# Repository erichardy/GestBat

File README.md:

# GestBat
Boîtier d'aide à la mise en charge des batteries de mon Vélo à Assistance Electrique (VAE)

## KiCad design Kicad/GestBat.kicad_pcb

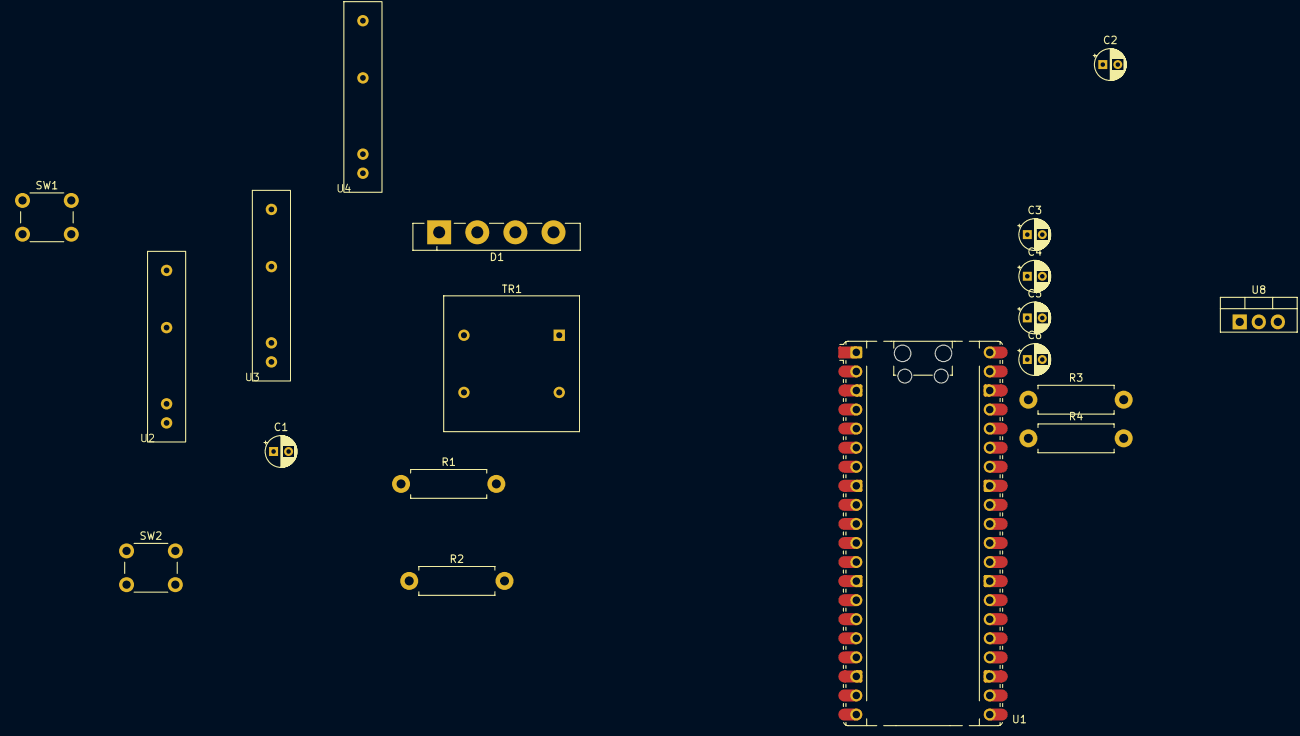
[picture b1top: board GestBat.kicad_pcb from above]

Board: 2 copper layers, 19 parts (0 on the bottom side), 14 nets, no tracks yet.

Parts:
C1, C5, C6: c=10u; CP_Radial_D4.0mm_P2.00mm
C2: c=1u; CP_Radial_D4.0mm_P2.00mm
C3, C4: c=1000u; CP_Radial_D4.0mm_P2.00mm
D1: GBU4M; Diode_Bridge_Vishay_GBU
R1: r=1M; R_Axial_DIN0411_L9.9mm_D3.6mm_P12.70mm_Horizontal
R2: r=6.8k; R_Axial_DIN0411_L9.9mm_D3.6mm_P12.70mm_Horizontal
R3: r=3.3k; R_Axial_DIN0411_L9.9mm_D3.6mm_P12.70mm_Horizontal
R4: r=1k; R_Axial_DIN0411_L9.9mm_D3.6mm_P12.70mm_Horizontal
SW1, SW2: SW_Push; SW_PUSH_6mm_H5mm
TR1: TRANSF1; Transformer_NF_ETAL_P3356
U1: eh_RP2040_pico; RaspberryPi_Pico_Common_Unspecified
U2, U3, U4: G3MB-202P
U8: LM7909_TO220; TO-220-3_Vertical

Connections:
/-9: C6.2, U8.3 (VO)
/MEAS_Current: C2.1, U1.31 (GPIO26)
/MEAS_Tension: R1.2, R2.2, U1.32 (GPIO27)
/VAC1: D1.3, SW1.2, TR1.1, U2.2 (LOAD2), U4.2 (LOAD2)
/VAC2: D1.2, SW2.2, U3.2 (LOAD2)
/ctrl-LOAD: U1.24 (GPIO18), U4.4 (Plus)
/ctrl-Main1: U1.21 (GPIO16), U2.4 (Plus)
/ctrl-Main2: U1.22 (GPIO17), U3.4 (Plus)
GND: C1.2, C2.2, C3.2, C4.1, C6.1, D1.4 (-), R2.1, TR1.3, U1.13 (GND), U2.3 (Moins), U3.3 (Moins), U4.3 (Moins), U8.1 (GND)
unnamed: C1.1, D1.1 (+), R1.1
unnamed: C4.2, U8.2 (VI)
unnamed: SW2.1, U3.1 (LOAD1)
unnamed: SW1.1, U2.1 (LOAD1)
unnamed: R3.2, R4.1

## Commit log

2026-06-08 TODO : doc
2026-06-08 add .gitignore
2026-06-08 start doc
2026-06-08 images
2026-06-08 doc in progress
